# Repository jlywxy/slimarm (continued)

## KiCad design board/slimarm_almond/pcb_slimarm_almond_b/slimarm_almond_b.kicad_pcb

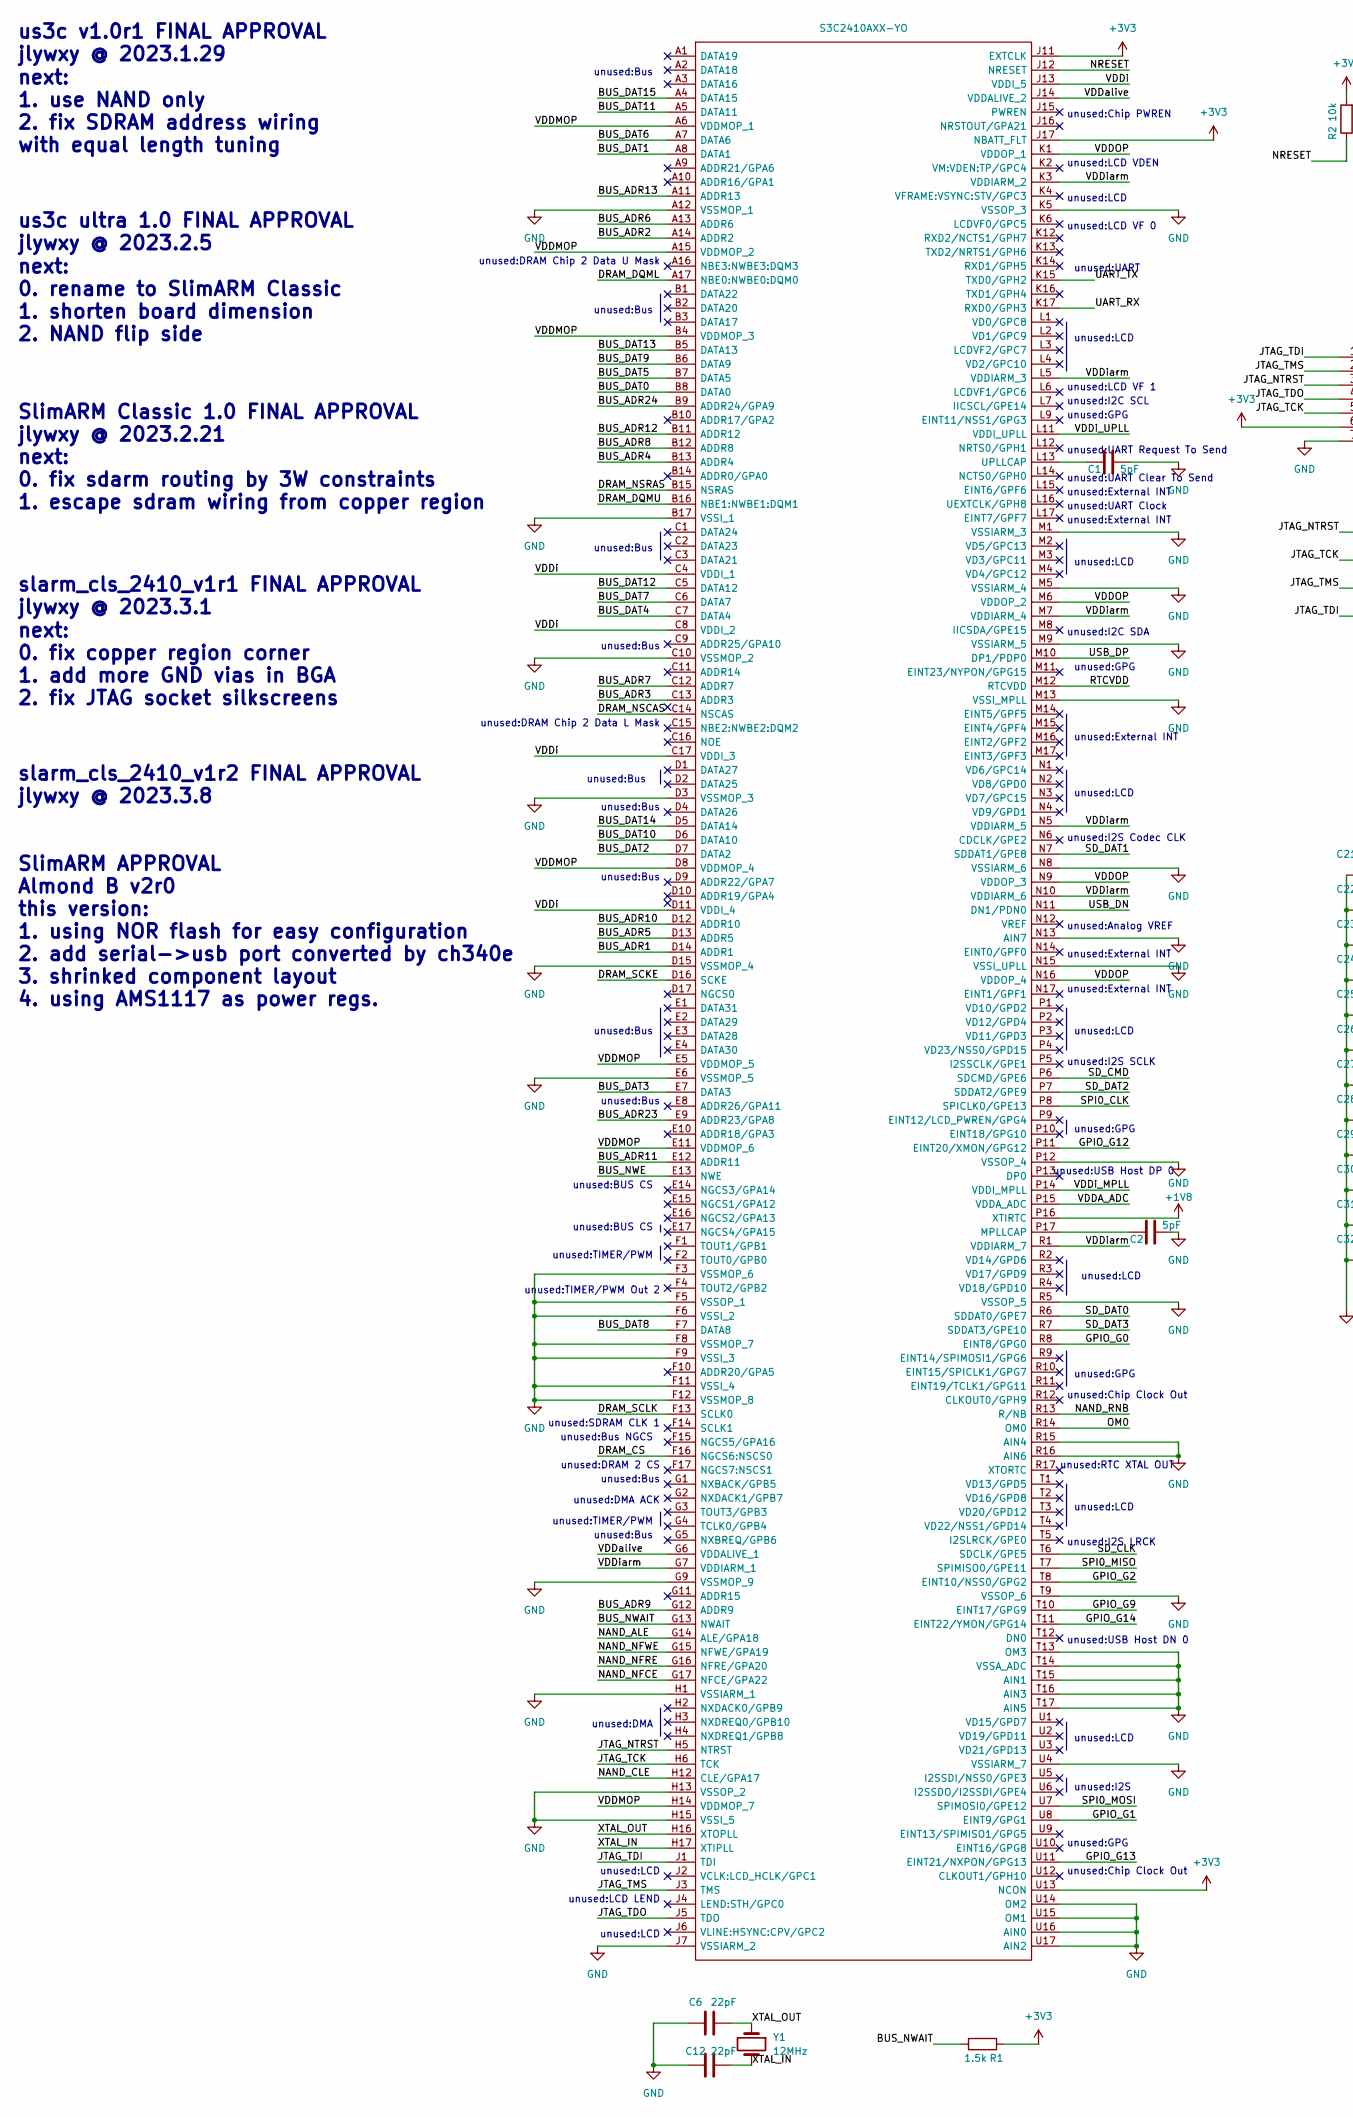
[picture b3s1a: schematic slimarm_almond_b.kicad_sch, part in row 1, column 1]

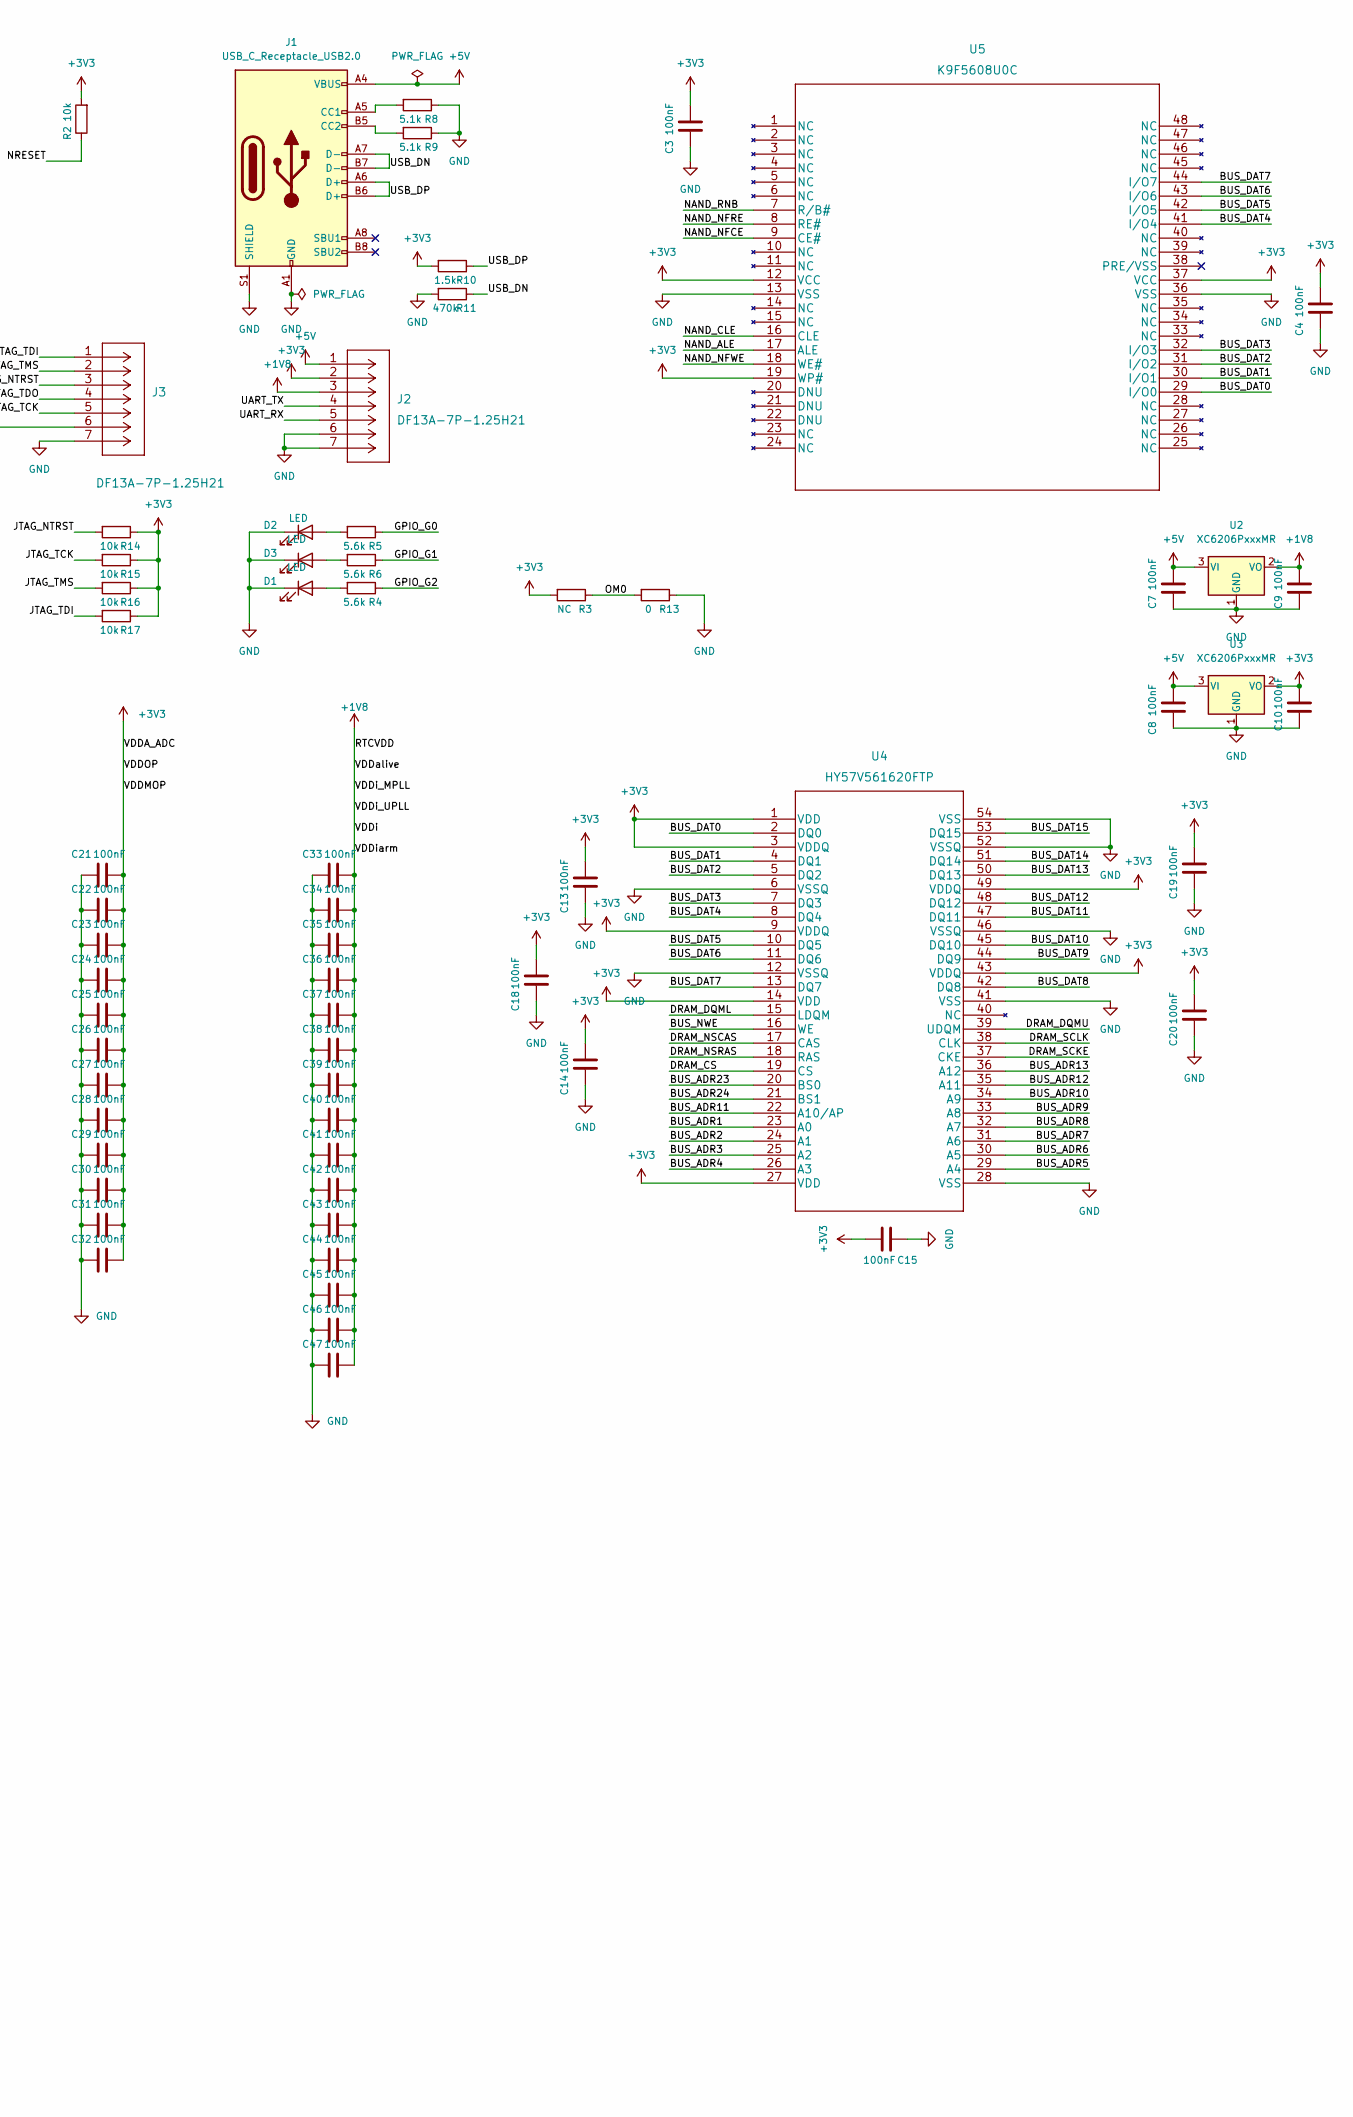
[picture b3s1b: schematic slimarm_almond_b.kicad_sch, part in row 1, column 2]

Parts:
C1, C2: 5pF; C_0402_1005Metric_Pad0.74x0.62mm_HandSolder
C3, C4, C7, C8, C9, C10, C13, C14, C15, C18, C19, C20, C21, C22, C23, C24, C25, C26, C27, C28, C29, C30, C31, C32, C33, C34, C35, C36, C37, C38, C39, C40, C41, C42, C43, C44, C45, C46, C47: 100nF; C_0402_1005Metric_Pad0.74x0.62mm_HandSolder
C6, C12: 22pF; C_0402_1005Metric_Pad0.74x0.62mm_HandSolder
D1, D2, D3: LED; LED_0603_1608Metric_Pad1.05x0.95mm_HandSolder
IC1: S3C2410AXX-YO; BGA272C80P17X17_1400X1400X116; Manufacturer_Part_Number S3C2410AXX-YO
J1: USB_C_Receptacle_USB2.0; USB_C_Receptacle_HRO_TYPE-C-31-M-12
J2, J3: DF13A-7P-1.25H21
R1, R10: 1.5k; R_0603_1608Metric_Pad0.98x0.95mm_HandSolder
R2, R14, R15, R16, R17: 10k; R_0603_1608Metric_Pad0.98x0.95mm_HandSolder
R3: NC; R_0603_1608Metric_Pad0.98x0.95mm_HandSolder
R4, R5, R6: 5.6k; R_0603_1608Metric_Pad0.98x0.95mm_HandSolder
R8, R9: 5.1k; R_0603_1608Metric_Pad0.98x0.95mm_HandSolder
R11: 470k; R_0603_1608Metric_Pad0.98x0.95mm_HandSolder
R13: 0; R_0603_1608Metric_Pad0.98x0.95mm_HandSolder
U2, U3: XC6206PxxxMR; SOT-23
U4: HY57V561620FTP
U5: K9F5608U0C; M29W640FB70N6E
Y1: 12MHz; Crystal_SMD_5032-2Pin_5.0x3.2mm

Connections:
+1V8: C9.2, C33.2, C34.2, C35.2, C36.2, C37.2, C38.2, C39.2, C40.2, C41.2, C42.2, C43.2, C44.2, C45.2, C46.2, C47.2, IC1.C4 (VDDI_1), IC1.C8 (VDDI_2), IC1.C17 (VDDI_3), IC1.D11 (VDDI_4), IC1.G6 (VDDALIVE_1), IC1.G7 (VDDIARM_1), IC1.J13 (VDDI_5), IC1.J14 (VDDALIVE_2), IC1.K3 (VDDIARM_2), IC1.L5 (VDDIARM_3), IC1.L11 (VDDI_UPLL), IC1.M7 (VDDIARM_4), IC1.M12 (RTCVDD), IC1.N5 (VDDIARM_5), IC1.N10 (VDDIARM_6), IC1.P14 (VDDI_MPLL), IC1.P16 (XTIRTC), IC1.R1 (VDDIARM_7), J2.3, U2.2 (VO)
+3V3: C3.2, C4.2, C10.2, C13.2, C14.2, C15.2, C18.2, C19.2, C20.2, C21.2, C22.2, C23.2, C24.2, C25.2, C26.2, C27.2, C28.2, C29.2, C30.2, C31.2, C32.2, IC1.A6 (VDDMOP_1), IC1.A15 (VDDMOP_2), IC1.B4 (VDDMOP_3), IC1.D8 (VDDMOP_4), IC1.E5 (VDDMOP_5), IC1.E11 (VDDMOP_6), IC1.H14 (VDDMOP_7), IC1.J11 (EXTCLK), IC1.J17 (NBATT_FLT), IC1.K1 (VDDOP_1), IC1.M6 (VDDOP_2), IC1.N9 (VDDOP_3), IC1.N16 (VDDOP_4), IC1.P15 (VDDA_ADC), IC1.U13 (NCON), J2.2, J3.6, R1.1, R2.2, R3.2, R10.2, R14.1, R15.1, R16.1, R17.1, U3.2 (VO), U4.1 (VDD), U4.3 (VDDQ), U4.9 (VDDQ), U4.14 (VDD), U4.27 (VDD), U4.43 (VDDQ), U4.49 (VDDQ), U5.12 (VCC), U5.19 (WP#), U5.37 (VCC)
+5V: C7.2, C8.2, J1.A4 (VBUS), J1.A9 (VBUS), J1.B4 (VBUS), J1.B9 (VBUS), J2.1, U2.3 (VI), U3.3 (VI)
/BUS_ADR1: IC1.D14 (ADDR1), U4.23 (A0)
/BUS_ADR2: IC1.A14 (ADDR2), U4.24 (A1)
/BUS_ADR3: IC1.C13 (ADDR3), U4.25 (A2)
/BUS_ADR4: IC1.B13 (ADDR4), U4.26 (A3)
/BUS_ADR5: IC1.D13 (ADDR5), U4.29 (A4)
/BUS_ADR6: IC1.A13 (ADDR6), U4.30 (A5)
/BUS_ADR7: IC1.C12 (ADDR7), U4.31 (A6)
/BUS_ADR8: IC1.B12 (ADDR8), U4.32 (A7)
/BUS_ADR9: IC1.G12 (ADDR9), U4.33 (A8)
/BUS_ADR10: IC1.D12 (ADDR10), U4.34 (A9)
/BUS_ADR11: IC1.E12 (ADDR11), U4.22 (A10/AP)
/BUS_ADR12: IC1.B11 (ADDR12), U4.35 (A11)
/BUS_ADR13: IC1.A11 (ADDR13), U4.36 (A12)
/BUS_ADR23: IC1.E9 (ADDR23/GPA8), U4.20 (BS0)
/BUS_ADR24: IC1.B9 (ADDR24/GPA9), U4.21 (BS1)
/BUS_DAT0: IC1.B8 (DATA0), U4.2 (DQ0), U5.29 (I/O0)
/BUS_DAT1: IC1.A8 (DATA1), U4.4 (DQ1), U5.30 (I/O1)
/BUS_DAT2: IC1.D7 (DATA2), U4.5 (DQ2), U5.31 (I/O2)
/BUS_DAT3: IC1.E7 (DATA3), U4.7 (DQ3), U5.32 (I/O3)
/BUS_DAT4: IC1.C7 (DATA4), U4.8 (DQ4), U5.41 (I/O4)
/BUS_DAT5: IC1.B7 (DATA5), U4.10 (DQ5), U5.42 (I/O5)
/BUS_DAT6: IC1.A7 (DATA6), U4.11 (DQ6), U5.43 (I/O6)
/BUS_DAT7: IC1.C6 (DATA7), U4.13 (DQ7), U5.44 (I/O7)
/BUS_DAT8: IC1.F7 (DATA8), U4.42 (DQ8)
/BUS_DAT9: IC1.B6 (DATA9), U4.44 (DQ9)
/BUS_DAT10: IC1.D6 (DATA10), U4.45 (DQ10)
/BUS_DAT11: IC1.A5 (DATA11), U4.47 (DQ11)
/BUS_DAT12: IC1.C5 (DATA12), U4.48 (DQ12)
/BUS_DAT13: IC1.B5 (DATA13), U4.50 (DQ13)
/BUS_DAT14: IC1.D5 (DATA14), U4.51 (DQ14)
/BUS_DAT15: IC1.A4 (DATA15), U4.53 (DQ15)
/BUS_NWAIT: IC1.G13 (NWAIT), R1.2
/BUS_NWE: IC1.E13 (NWE), U4.16 (WE)
/DRAM_CS: IC1.F16 (NGCS6:NSCS0), U4.19 (CS)
/DRAM_DQML: IC1.A17 (NBE0:NWBE0:DQM0), U4.15 (LDQM)
/DRAM_DQMU: IC1.B16 (NBE1:NWBE1:DQM1), U4.39 (UDQM)
/DRAM_NSCAS: IC1.C14 (NSCAS), U4.17 (CAS)
/DRAM_NSRAS: IC1.B15 (NSRAS), U4.18 (RAS)
/DRAM_SCKE: IC1.D16 (SCKE), U4.37 (CKE)
/DRAM_SCLK: IC1.F13 (SCLK0), U4.38 (CLK)
/GPIO_G0: IC1.R8 (EINT8/GPG0), R5.1
/GPIO_G1: IC1.U8 (EINT9/GPG1), R6.1
/GPIO_G2: IC1.T8 (EINT10/NSS0/GPG2), R4.1
/GPIO_G9: IC1.T10 (EINT17/GPG9)
/GPIO_G12: IC1.P11 (EINT20/XMON/GPG12)
/GPIO_G13: IC1.U11 (EINT21/NXPON/GPG13)
/GPIO_G14: IC1.T11 (EINT22/YMON/GPG14)
/JTAG_NTRST: IC1.H5 (NTRST), J3.3, R14.2
/JTAG_TCK: IC1.H6 (TCK), J3.5, R15.2
/JTAG_TDI: IC1.J1 (TDI), J3.1, R17.2
/JTAG_TDO: IC1.J5 (TDO), J3.4
/JTAG_TMS: IC1.J3 (TMS), J3.2, R16.2
/NAND_ALE: IC1.G14 (ALE/GPA18), U5.17 (ALE)
/NAND_CLE: IC1.H12 (CLE/GPA17), U5.16 (CLE)
/NAND_NFCE: IC1.G17 (NFCE/GPA22), U5.9 (CE#)
/NAND_NFRE: IC1.G16 (NFRE/GPA20), U5.8 (RE#)
/NAND_NFWE: IC1.G15 (NFWE/GPA19), U5.18 (WE#)
/NAND_RNB: IC1.R13 (R/NB), U5.7 (R/B#)
/NRESET: IC1.J12 (NRESET), R2.1
/OM0: IC1.R14 (OM0), R3.1, R13.2
/SD_CLK: IC1.T6 (SDCLK/GPE5)
/SD_CMD: IC1.P6 (SDCMD/GPE6)
/SD_DAT0: IC1.R6 (SDDAT0/GPE7)
/SD_DAT1: IC1.N7 (SDDAT1/GPE8)
/SD_DAT2: IC1.P7 (SDDAT2/GPE9)
/SD_DAT3: IC1.R7 (SDDAT3/GPE10)
/SPI0_CLK: IC1.P8 (SPICLK0/GPE13)
/SPI0_MISO: IC1.T7 (SPIMISO0/GPE11)
/SPI0_MOSI: IC1.U7 (SPIMOSI0/GPE12)
/UART_RX: IC1.K17 (RXD0/GPH3), J2.5
/UART_TX: IC1.K15 (TXD0/GPH2), J2.4
/USB_DN: IC1.N11 (DN1/PDN0), J1.A7 (D-), J1.B7 (D-), R11.1
/USB_DP: IC1.M10 (DP1/PDP0), J1.A6 (D+), J1.B6 (D+), R10.1
/XTAL_IN: C12.2, IC1.H17 (XTIPLL), Y1.2
/XTAL_OUT: C6.2, IC1.H16 (XTOPLL), Y1.1
GND: C1.2, C2.2, C3.1, C4.1, C6.1, C7.1, C8.1, C9.1, C10.1, C12.1, C13.1, C14.1, C15.1, C18.1, C19.1, C20.1, C21.1, C22.1, C23.1, C24.1, C25.1, C26.1, C27.1, C28.1, C29.1, C30.1, C31.1, C32.1, C33.1, C34.1, C35.1, C36.1, C37.1, C38.1, C39.1, C40.1, C41.1, C42.1, C43.1, C44.1, C45.1, C46.1, C47.1, D1.1 (K), D2.1 (K), D3.1 (K), IC1.A12 (VSSMOP_1), IC1.B17 (VSSI_1), IC1.C10 (VSSMOP_2), IC1.D3 (VSSMOP_3), IC1.D15 (VSSMOP_4), IC1.E6 (VSSMOP_5), IC1.F3 (VSSMOP_6), IC1.F5 (VSSOP_1), IC1.F6 (VSSI_2), IC1.F8 (VSSMOP_7), IC1.F9 (VSSI_3), IC1.F11 (VSSI_4), IC1.F12 (VSSMOP_8), IC1.G9 (VSSMOP_9), IC1.H1 (VSSIARM_1), IC1.H13 (VSSOP_2), IC1.H15 (VSSI_5), IC1.J7 (VSSIARM_2), IC1.K5 (VSSOP_3), IC1.M1 (VSSIARM_3), IC1.M5 (VSSIARM_4), IC1.M9 (VSSIARM_5), IC1.M13 (VSSI_MPLL), IC1.N8 (VSSIARM_6), IC1.N13 (AIN7), IC1.N15 (VSSI_UPLL), IC1.P12 (VSSOP_4), IC1.R5 (VSSOP_5), IC1.R15 (AIN4), IC1.R16 (AIN6), IC1.T9 (VSSOP_6), IC1.T13 (OM3), IC1.T14 (VSSA_ADC), IC1.T15 (AIN1), IC1.T16 (AIN3), IC1.T17 (AIN5), IC1.U4 (VSSIARM_7), IC1.U14 (OM2), IC1.U15 (OM1), IC1.U16 (AIN0), IC1.U17 (AIN2), J1.A1 (GND), J1.A12 (GND), J1.B1 (GND), J1.B12 (GND), J1.S1 (SHIELD), J2.6, J2.7, J3.7, R8.1, R9.1, R11.2, R13.1, U2.1 (GND), U3.1 (GND), U4.6 (VSSQ), U4.12 (VSSQ), U4.28 (VSS), U4.41 (VSS), U4.46 (VSSQ), U4.52 (VSSQ), U4.54 (VSS), U5.13 (VSS), U5.36 (VSS)
unnamed: C1.1, IC1.L13 (UPLLCAP)
unnamed: C2.1, IC1.P17 (MPLLCAP)
unnamed: D1.2 (A), R4.2
unnamed: D2.2 (A), R5.2
unnamed: D3.2 (A), R6.2
unnamed: J1.A5 (CC1), R8.2
unnamed: J1.B5 (CC2), R9.2

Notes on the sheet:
unused:DRAM Chip 2 Data U Mask
unused:DRAM Chip 2 Data L Mask
unused:Bus
unused:TIMER/PWM Out 2
unused:I2S LRCK
unused:LCD
unused:UART
slarm_cls_2410_v1r2 FINAL APPROVAL jlywxy @ 2023.3.8
unused:UART Clear To Send
next: 0. fix copper region corner 1. add more GND vias in BGA 2. fix JTAG socket silkscreens
unused:External INT
unused:DRAM 2 CS
unused:GPG
slarm_cls_2410_v1r1 FINAL APPROVAL jlywxy @ 2023.3.1
unused:RTC XTAL OUT
unused:LCD VF 0
unused:I2S
unused:Chip Clock Out
SlimARM APPROVAL Almond B v2r0 this version: 1. using NOR flash for easy configuration 2. add serial->usb port converted by ch340e 3. shrinked component layout 4. using AMS1117 as power regs.
unused:USB Host DN 0
unused:LCD LEND
unused:LCD VF 1
unused:LCD VDEN
unused:I2C SCL
unused:TIMER/PWM
unused:BUS CS
unused:Chip Clock Out
unused:I2S Codec CLK
unused:USB Host DP 0
unused:DMA ACK
unused:Chip PWREN
next: 0. rename to SlimARM Classic 1. shorten board dimension 2. NAND flip side
unused:UART Request To Send
us3c ultra 1.0 FINAL APPROVAL jlywxy @ 2023.2.5
unused:Bus NGCS
unused:I2S SCLK
unused:SDRAM CLK 1
next: 1. use NAND only 2. fix SDRAM address wiring with equal length tuning
unused:DMA
SlimARM Classic 1.0 FINAL APPROVAL jlywxy @ 2023.2.21 next: 0. fix sdarm routing by 3W constraints 1. escape sdram wiring from copper region

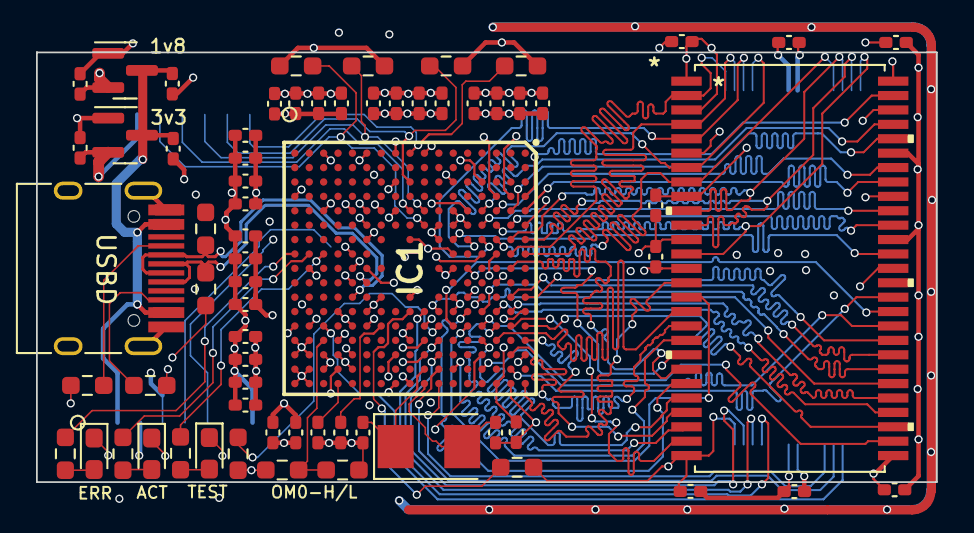
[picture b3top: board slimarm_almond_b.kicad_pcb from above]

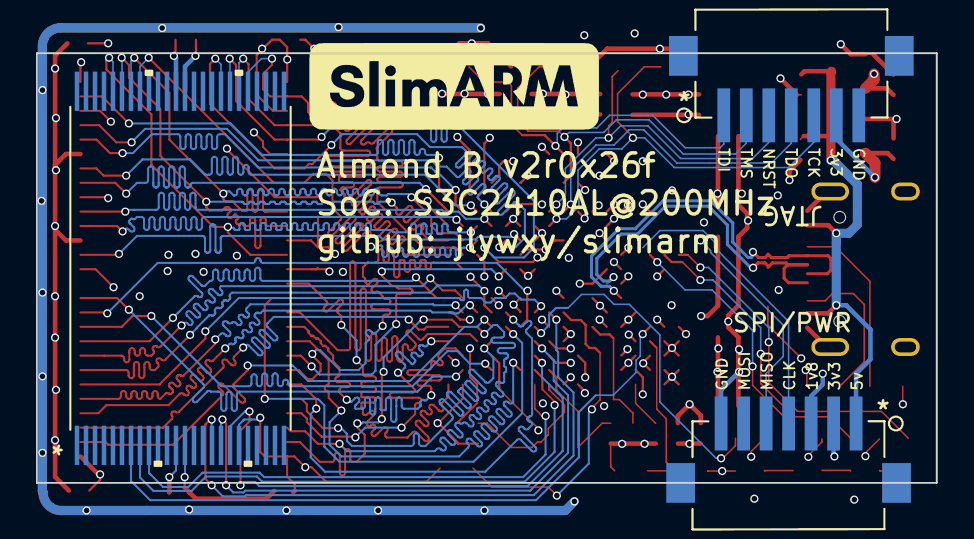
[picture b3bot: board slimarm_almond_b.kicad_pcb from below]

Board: 4 copper layers, 50.0 x 23.9 mm, 70 parts (3 on the bottom side), 73 nets.

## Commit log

2023-02-15 init commit
2023-02-16 changing plan
2023-02-23 project status update
2023-03-01 project plan update
2023-03-11 new project plan; slarm_cls_2410 board
2023-05-10 23x1fe
2023-05-15 fixed carambola board; board 3d models
2023-05-20 23x208
2023-05-27 23x20f
2023-07-02 23x2bf
2023-07-10 23x2c7
2023-07-10 23x2c7-part2(Carambola)
2023-07-23 23x2d3
2023-08-01 23x321
